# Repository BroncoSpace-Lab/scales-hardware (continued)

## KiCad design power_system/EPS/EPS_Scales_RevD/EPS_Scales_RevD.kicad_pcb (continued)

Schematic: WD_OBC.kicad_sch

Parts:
C42, C43, C44: 220u; CAP-SMD_BD6.3-L6.6-W6.6-FD; LCSC Part C171665
C63, C64, C65, C66, C67: 10u; C_1210_3225Metric; MPN GRT188R61C106KE13D
D10, D12: 1N4151WS; SOD2512X116N; MPN 1N4151WS-E3-08
D11: GREEN; LED_0603_1608Metric; MPN 150060GS75000
J18: Conn_01x04; PinSocket_1x04_P2.54mm_Vertical
JP5: SolderJumper_2_Open; SolderJumper-2_P1.3mm_Open_RoundedPad1.0x1.5mm
R84: 10 (1206); R_1206_3216Metric; MPN ESR18EZPF10R0; LCSC C17903
R85, R86, R87, R91, R92: 10k; R_0603_1608Metric; MPN RMCF0603FT10K0; LCSC C13564
R88, R89, R90: 3.0k; R_0603_1608Metric; MPN RMCF0603FT3K00; LCSC C4211
R93, R95: 1k; R_0603_1608Metric; MPN RMCF0603FT1K00; LCSC C13163
R94, R96, R97, R98, R100: 100k; R_0603_1608Metric; MPN RMCF0603FT100K; LCSC C14675
R99: 4.7M; R_0603_1608Metric; MPN RMCF0603FT4M70
TP48, TP49, TP50, TP51, TP52, TP53: TestPoint; TestPoint_Pad_1.0x1.0mm
U14: TLV1704; TSSOP-14_4.4x5mm_P0.65mm; MPN TLV1704AQPWRQ1; LCSC C181596

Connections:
+3.3V_OBC: D10.2 (A), J18.1, J18.2; also elsewhere on the board
/OBC_Subsystem/WD_OBC/WDT-VIN: C42.1, C43.1, C44.1, R84.2, R85.1, R94.1, R100.2, TP48.1, U14.3 (V+)
/OBC_Subsystem/WD_OBC/WDT-VP: R88.2, R89.1, U14.5 (+)
GND: C42.2, C43.2, C44.2, C64.1, C65.1, C66.1, C67.1, D11.1 (K), J18.3, J18.4, R89.2, R91.2, U14.12 (V-); also elsewhere on the board
unnamed: C63.2, R91.1, R92.1
unnamed: D10.1 (K), R84.1
unnamed: D11.2 (A), R90.2
unnamed: D12.2 (A), R97.1
unnamed: D12.1 (K), R98.2, R99.1, R100.1, TP52.1, U14.11 (+), U14.14
unnamed: JP5.1 (A), TP53.1, U14.13
unnamed: R85.2, R86.1, R96.2
unnamed: R93.1, U14.2
unnamed: R95.1, U14.1
unnamed: R92.2, U14.4 (-)
unnamed: C64.2, R93.2, R94.2, TP50.1, U14.7 (+)
unnamed: R87.2, R88.1, U14.6 (-)
unnamed: R96.1, R98.1, U14.9 (+)
unnamed: C65.2, C66.2, R95.2, R97.2, R99.2, TP51.1, U14.8 (-)
unnamed: C67.2, R86.2, R87.1, U14.10 (-)
WDT_WDI_OBC: C63.1, R90.1, TP49.1; also elsewhere on the board
~WD_EN_OBC: JP5.2 (B); also elsewhere on the board

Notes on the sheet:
Oscillator
Output buffer
DC block and pulse detector
D5 and D7 MUST be 1N4151WS
Disable shutdown during initial power up.
Select 15V-25V on C21, C22, C23
Pulse integrator
WDT enabled when soldered
TLV1704AMPWPSEP is the radiation tolerant version. Use TLV1704AQPWRQ1 for non-flight C3 boards.
External Watch-Dog Timer
C112+C114 and R62+R63 set the WDT frequency
~ 24 s period (36 s on power up)
660uF Capacitance used to keep WD output high after reset for 2-3s to allow for subsystem reboot
WD_EN_OBC goes to EN of the load switch controller

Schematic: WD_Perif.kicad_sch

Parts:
C6, C34, C35: 220u; CAP-SMD_BD6.3-L6.6-W6.6-FD; LCSC Part C171665
C7, C8, C9, C17, C33: 10u; C_1210_3225Metric; MPN GRT188R61C106KE13D
D6, D8: 1N4151WS; SOD2512X116N; MPN 1N4151WS-E3-08
D7: GREEN; LED_0603_1608Metric; MPN 150060GS75000
J7: Conn_01x04; PinSocket_1x04_P2.54mm_Vertical
JP2: SolderJumper_2_Open; SolderJumper-2_P1.3mm_Open_RoundedPad1.0x1.5mm
R2: 10 (1206); R_1206_3216Metric; MPN ESR18EZPF10R0; LCSC C17903
R8, R9, R29, R33, R38: 10k; R_0603_1608Metric; MPN RMCF0603FT10K0; LCSC C13564
R30, R31, R32: 3.0k; R_0603_1608Metric; MPN RMCF0603FT3K00; LCSC C4211
R39, R51: 1k; R_0603_1608Metric; MPN RMCF0603FT1K00; LCSC C13163
R49, R67, R68, R69, R71: 100k; R_0603_1608Metric; MPN RMCF0603FT100K; LCSC C14675
R70: 4.7M; R_0603_1608Metric; MPN RMCF0603FT4M70
TP5, TP6, TP7, TP8, TP9, TP15: TestPoint; TestPoint_Pad_1.0x1.0mm
U6: TLV1704; TSSOP-14_4.4x5mm_P0.65mm; MPN TLV1704AQPWRQ1; LCSC C181596

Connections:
+5V_Perif: D6.2 (A), J7.1, J7.2; also elsewhere on the board
/Perif_Subsystem/WD_Perif/WDT-VIN: C6.1, C34.1, C35.1, R2.2, R8.1, R49.1, R71.2, TP5.1, U6.3 (V+)
/Perif_Subsystem/WD_Perif/WDT-VP: R30.2, R31.1, U6.5 (+)
GND: C6.2, C8.1, C9.1, C17.1, C33.1, C34.2, C35.2, D7.1 (K), J7.3, J7.4, R31.2, R33.2, U6.12 (V-); also elsewhere on the board
unnamed: C7.2, R33.1, R38.1
unnamed: D6.1 (K), R2.1
unnamed: D7.2 (A), R32.2
unnamed: D8.2 (A), R68.1
unnamed: D8.1 (K), R69.2, R70.1, R71.1, TP9.1, U6.11 (+), U6.14
unnamed: JP2.1 (A), TP15.1, U6.13
unnamed: R39.1, U6.2
unnamed: R51.1, U6.1
unnamed: R8.2, R9.1, R67.2
unnamed: R38.2, U6.4 (-)
unnamed: C8.2, R39.2, R49.2, TP7.1, U6.7 (+)
unnamed: R29.2, R30.1, U6.6 (-)
unnamed: R67.1, R69.1, U6.9 (+)
unnamed: C9.2, C17.2, R51.2, R68.2, R70.2, TP8.1, U6.8 (-)
unnamed: C33.2, R9.2, R29.1, U6.10 (-)
WDT_WDI_Perif: C7.1, R32.1, TP6.1; also elsewhere on the board
~WD_EN_PERIF: JP2.2 (B); also elsewhere on the board

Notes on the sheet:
External Watch-Dog Timer
Output buffer
TLV1704AMPWPSEP is the radiation tolerant version. Use TLV1704AQPWRQ1 for non-flight C3 boards.
~ 24 s period (36 s on power up)
Disable shutdown during initial power up.
DC block and pulse detector
WDT enabled when soldered
D5 and D7 MUST be 1N4151WS
Pulse integrator
Oscillator
C112+C114 and R62+R63 set the WDT frequency
Select 15V-25V on C21, C22, C23
WD_EN_Perif goes to EN of the load switch controller
660uF Capacitance used to keep WD output high after reset for 2-3s to allow for subsystem reboot
Pulled down. Holds Perif board off until toggled by OBC_PERIF_EN is held high by the OBC

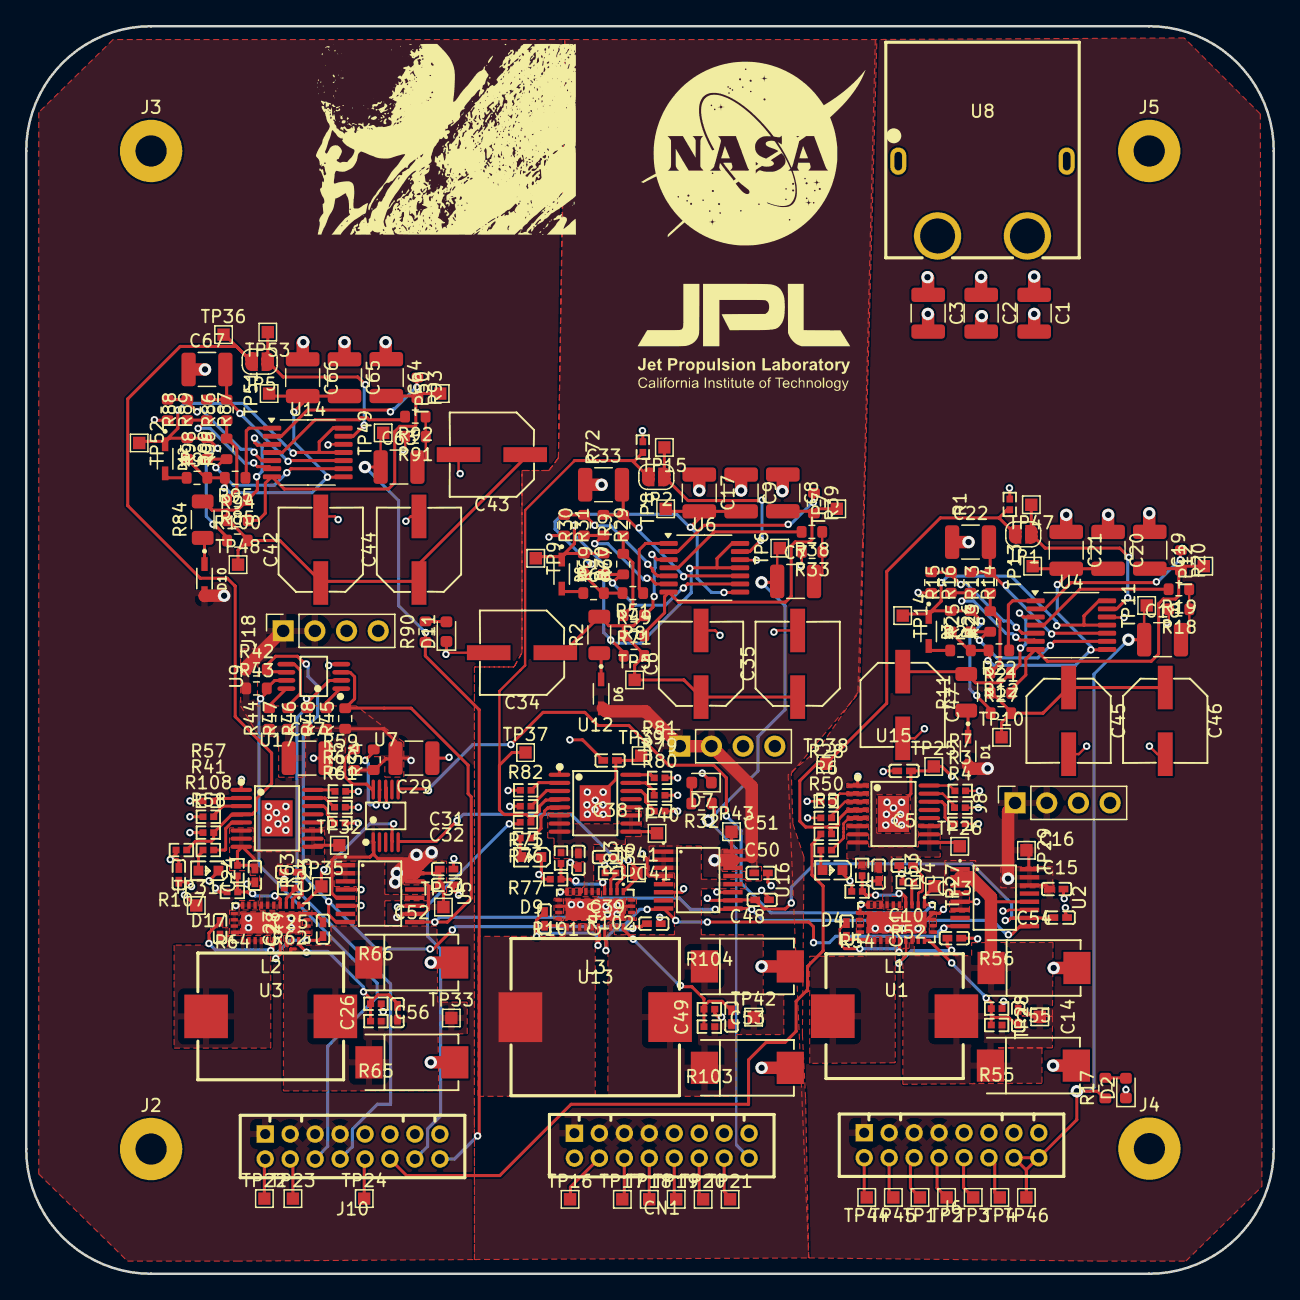
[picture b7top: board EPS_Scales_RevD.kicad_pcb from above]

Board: 4 copper layers, 100.0 x 100.0 mm, 253 parts (0 on the bottom side), 139 nets.

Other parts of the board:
C1, C2, C3: 10u; C_1210_3225Metric
J2, J3, J4, J5: Conn_01x01_Socket; MountingHole_2.5mm_Pad
U8: XT60PW-F_C428722; TH_2P-XT60PW-F

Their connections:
+V_Batt: C1.1, C2.1, C3.1, U8.3 (+); also elsewhere on the board
GND: C1.2, C2.2, C3.2, J2.1, J3.1, J4.1, J5.1, U8.1, U8.2, U8.4 (-); also elsewhere on the board
